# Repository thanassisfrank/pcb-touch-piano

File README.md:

# pcb-touch-piano

A project to create a small piano style synth on a pcb with capacitive touch input, powered by a coin cell. The MCU is the Atmega328pb with firmware written in C.

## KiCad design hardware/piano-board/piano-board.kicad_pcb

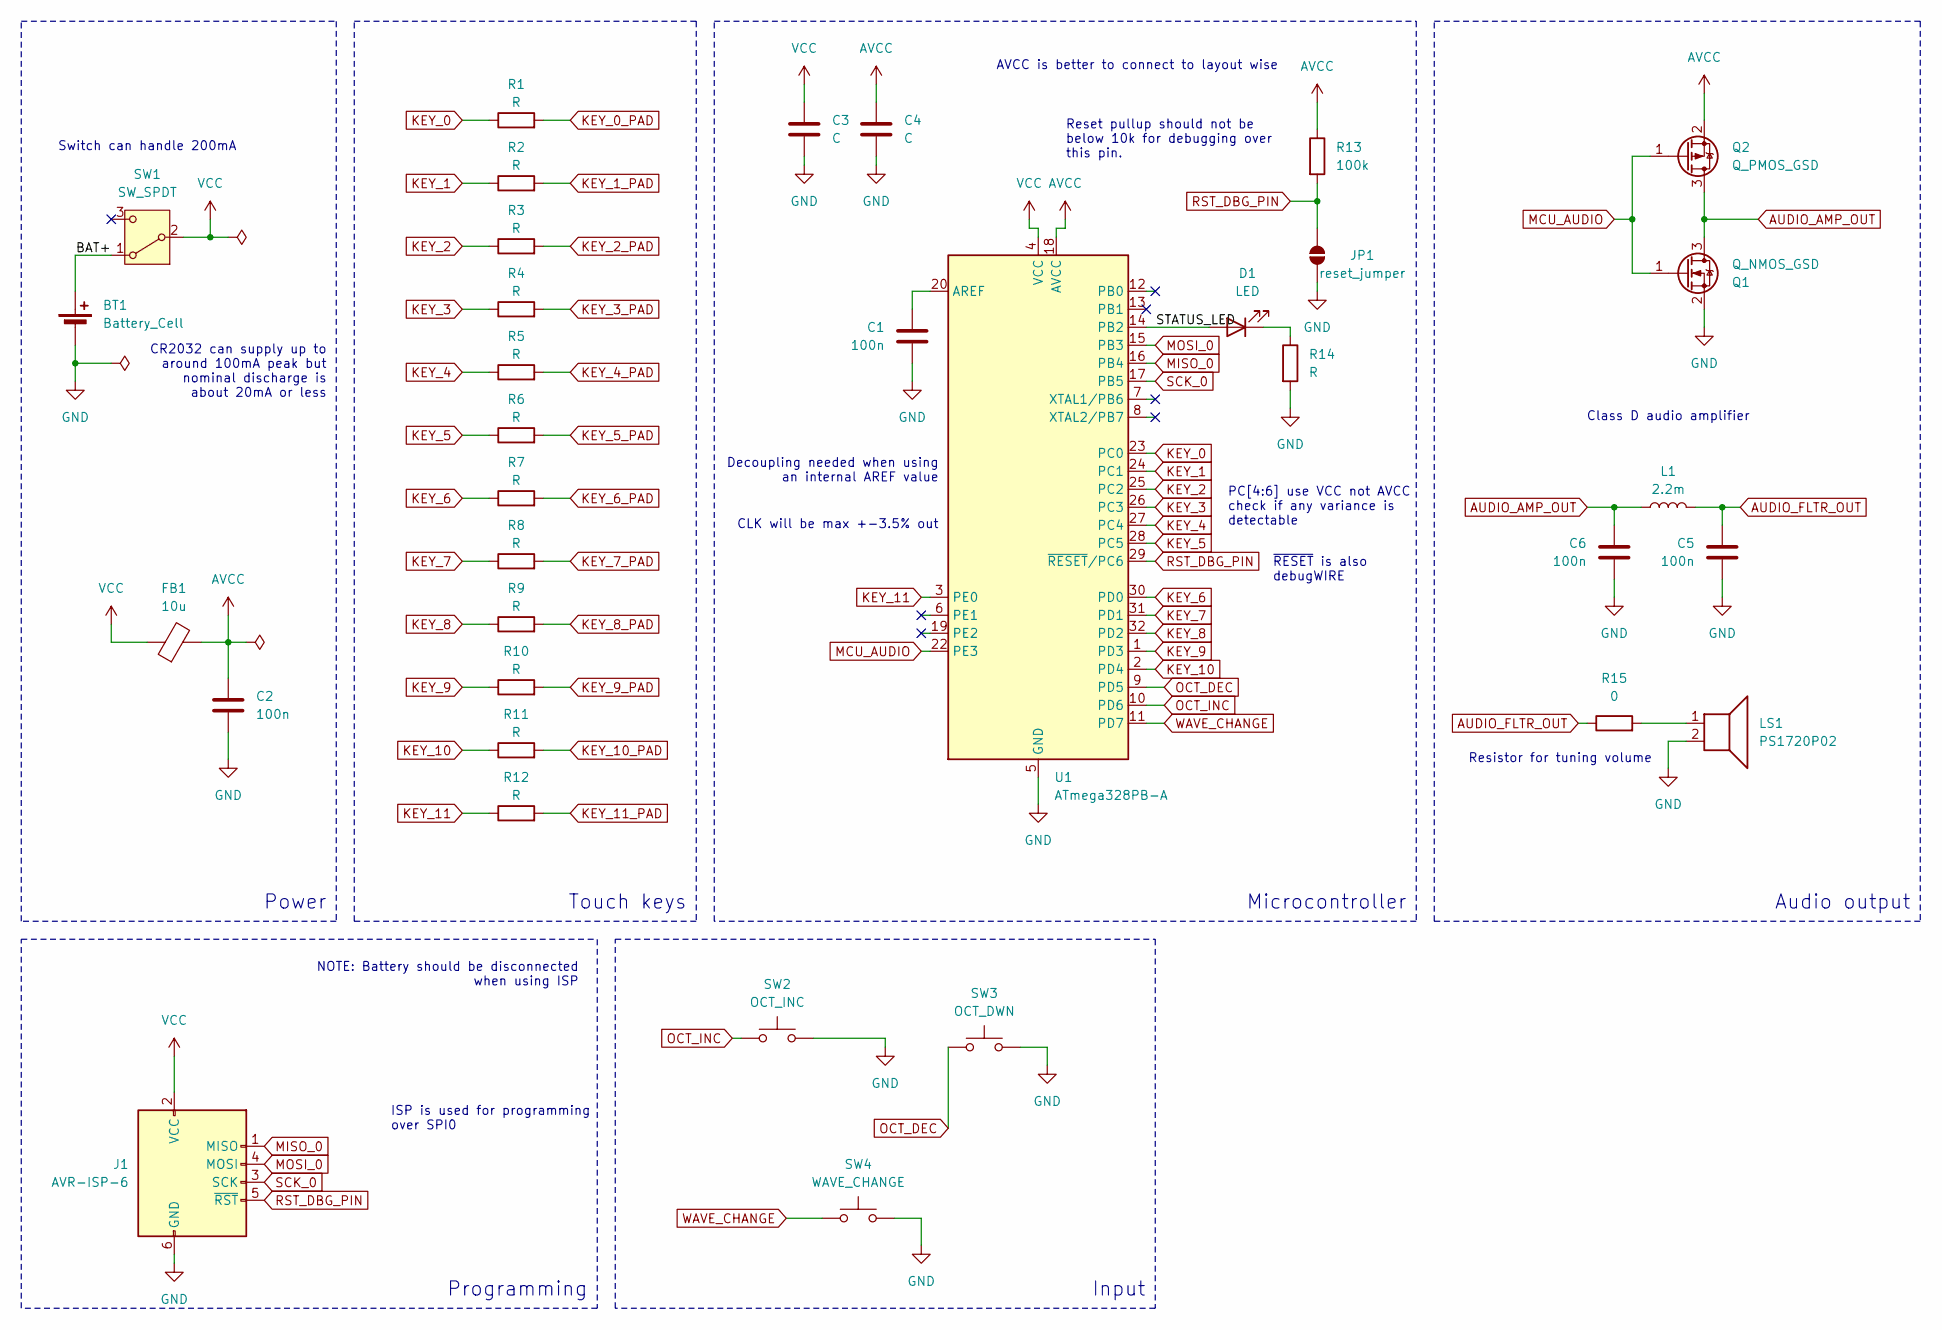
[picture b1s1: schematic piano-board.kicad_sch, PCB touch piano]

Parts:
BT1: Battery_Cell; MP000360
C1, C2, C5, C6: 100n; C_0603_1608Metric_Pad1.08x0.95mm_HandSolder
C3, C4: C; C_0603_1608Metric_Pad1.08x0.95mm_HandSolder
D1: LED; LED_0603_1608Metric_Pad1.05x0.95mm_HandSolder
FB1: 10u; R_0603_1608Metric_Pad0.98x0.95mm_HandSolder
J1: AVR-ISP-6; PinHeader_2x03_P2.54mm_Vertical
JP1: reset_jumper; SolderJumper-2_P1.3mm_Open_RoundedPad1.0x1.5mm
L1: 2.2m; L_Coilcraft_LPS4018
LS1: PS1720P02
Q1: Q_NMOS_GSD; SOT-23
Q2: Q_PMOS_GSD; SOT-23
R1, R2, R3, R4, R5, R6, R7, R8, R9, R10, R11, R12, R14: R; R_0603_1608Metric_Pad0.98x0.95mm_HandSolder
R13: 100k; R_0603_1608Metric_Pad0.98x0.95mm_HandSolder
R15: 0; R_0603_1608Metric_Pad0.98x0.95mm_HandSolder
SW1: SW_SPDT; SW_SPDT_TEC_1825232-1
SW2: OCT_INC; SW_PUSH_ADAFRUIT_SMALL
SW3: OCT_DWN; SW_PUSH_ADAFRUIT_SMALL
SW4: WAVE_CHANGE; SW_PUSH_ADAFRUIT_SMALL
U1: ATmega328PB-A; TQFP-32_7x7mm_P0.8mm

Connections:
/BAT+: BT1.1 (+), SW1.1 (A)
/STATUS_LED: D1.2 (A), U1.14 (PB2)
AUDIO_AMP_OUT: C6.1, L1.1, Q1.3 (D), Q2.3 (D)
AUDIO_FLTR_OUT: C5.1, L1.2, R15.1
AVCC: C2.1, C4.1, FB1.2, Q2.2 (S), R13.1, U1.18 (AVCC)
GND: BT1.2 (-), C1.1, C2.2, C3.2, C4.2, C5.2, C6.2, J1.6 (GND), JP1.1 (A), LS1.2, Q1.2 (S), R14.2, SW2.2, SW3.2, SW4.2, U1.5 (GND), U1.21 (GND)
KEY_0: R1.1, U1.23 (PC0)
KEY_0_PAD: R1.2
KEY_1: R2.1, U1.24 (PC1)
KEY_1_PAD: R2.2
KEY_2: R3.1, U1.25 (PC2)
KEY_2_PAD: R3.2
KEY_3: R4.1, U1.26 (PC3)
KEY_3_PAD: R4.2
KEY_4: R5.1, U1.27 (PC4)
KEY_4_PAD: R5.2
KEY_5: R6.1, U1.28 (PC5)
KEY_5_PAD: R6.2
KEY_6: R7.1, U1.30 (PD0)
KEY_6_PAD: R7.2
KEY_7: R8.1, U1.31 (PD1)
KEY_7_PAD: R8.2
KEY_8: R9.1, U1.32 (PD2)
KEY_8_PAD: R9.2
KEY_9: R10.1, U1.1 (PD3)
KEY_9_PAD: R10.2
KEY_10: R11.1, U1.2 (PD4)
KEY_10_PAD: R11.2
KEY_11: R12.1, U1.3 (PE0)
KEY_11_PAD: R12.2
MCU_AUDIO: Q1.1 (G), Q2.1 (G), U1.22 (PE3)
MISO_0: J1.1 (MISO), U1.16 (PB4)
MOSI_0: J1.4 (MOSI), U1.15 (PB3)
unnamed: D1.1 (K), R14.1
unnamed: LS1.1, R15.2
unnamed: C1.2, U1.20 (AREF)
OCT_DEC: SW3.1, U1.9 (PD5)
OCT_INC: SW2.1, U1.10 (PD6)
RST_DBG_PIN: J1.5 (~RST), JP1.2 (B), R13.2, U1.29 (~RESET/PC6)
SCK_0: J1.3 (SCK), U1.17 (PB5)
VCC: C3.1, FB1.1, J1.2 (VCC), SW1.2 (B), U1.4 (VCC)
WAVE_CHANGE: SW4.1, U1.11 (PD7)

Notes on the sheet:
CR2032 can supply up to around 100mA peak but nominal discharge is about 20mA or less
Input
Audio output
NOTE: Battery should be disconnected when using ISP
Programming
~{RESET} is also debugWIRE
Class D audio amplifier
Power
Touch keys
Microcontroller
Reset pullup should not be below 10k for debugging over this pin.
CLK will be max +-3.5% out
Decoupling needed when using an internal AREF value
ISP is used for programming over SPI0
Switch can handle 200mA
AVCC is better to connect to layout wise
Resistor for tuning volume
PC[4:6] use VCC not AVCC check if any variance is detectable

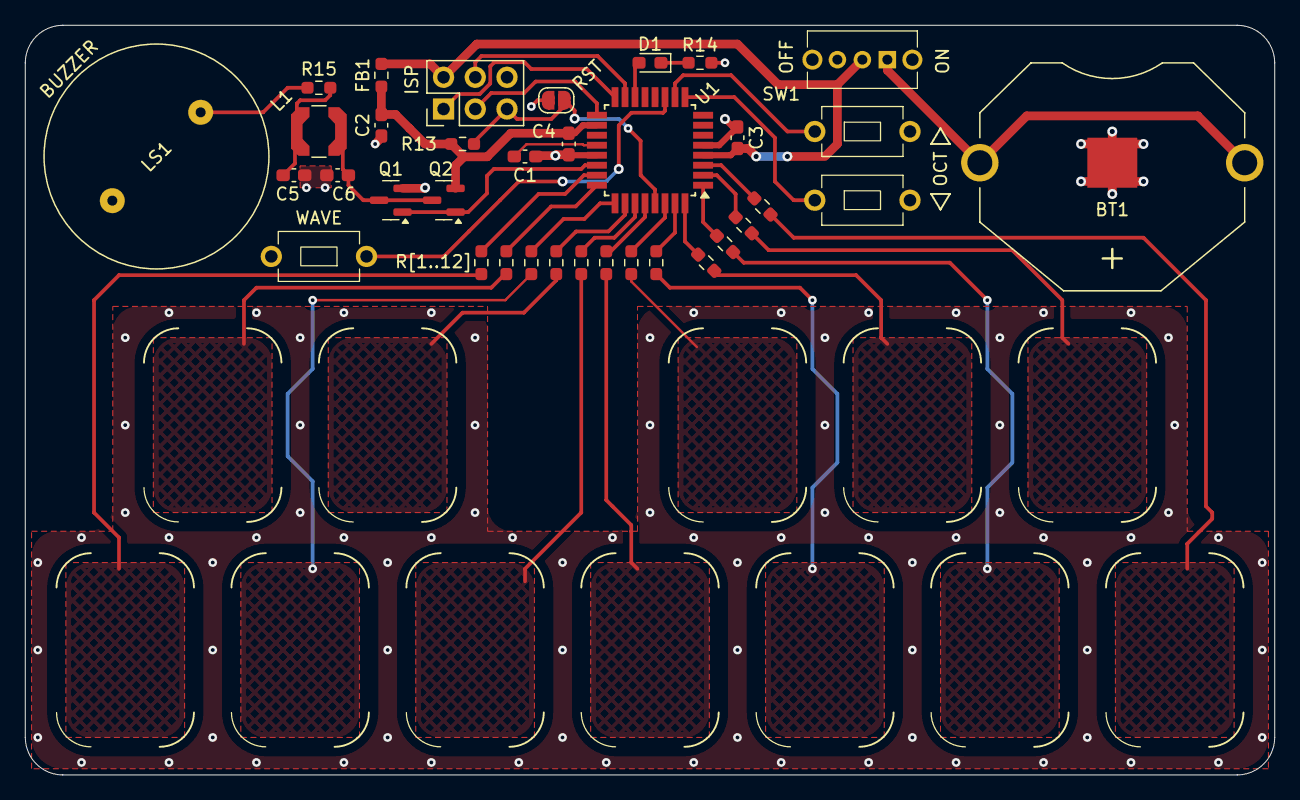
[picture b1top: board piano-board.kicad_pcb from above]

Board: 2 copper layers, 100.0 x 60.0 mm, 35 parts (0 on the bottom side), 30 nets.

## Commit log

2024-11-22 Create project
2024-11-23 Create initial pcb schematic
2024-11-24 Design audio output on schematic
2024-11-24 Assign footprints
2024-11-25 Create initial board layout
2024-11-25 Improve CR2032 holder footprint
2024-11-27 Route key connections
2024-11-27 Re-assign key pins on MCU
2024-11-28 Route all signals
2024-12-02 Add status LED
2024-12-03 Polish for manufacturing
2025-02-15 Create led flash test firmware
2025-02-15 Add ptc library
2025-05-14 Implement touch sensing for one key
2025-06-11 Sense touch on all keys
2025-06-11 Generate square-waves when keys are pressed
2025-06-14 Add image to README
2025-06-18 Implement basic gpio hal
2025-06-19 Set register values directly when touch sensing
2025-06-19 Add interrupt detection to buttons
2025-06-19 Implement button functions with simple debouncing
2025-06-19 Increase octave range
2025-06-25 Split sound generation from main
2025-06-25 Add saw wave output
2025-06-25 Add sine wave output
2025-06-26 Remove changes to global interrupts outside of main
2025-06-26 Make capacitive key charge atomic
2025-06-26 Make DDS PWM TOP configurable
2025-06-26 Remove delay in main loop
